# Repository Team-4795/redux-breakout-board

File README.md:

# rio-RGB_LED-buffer-board
a pcb that mounts to a RoboRIO and buffers the data stream for WS2812b and similar LED strips

The RoboRIO can generate a data stream for addressable "smart" LED
strips built from WS2812b and similar LEDs.  This data comes out on
one of the PWM ports, but is much faster than the typical "servo" PWM
data.  As such, it is more sensitive to signal integrity issues,
especially when splitting it to drive multiple LED strips with
identical data.

The tutorial and circuit board here is inspired by a discussion on the
Chief Delphi forums https://www.chiefdelphi.com/t/wrong-colors-from-ws2812-led-strips-driven-by-roborio/434199

The basic idea is that we use one WS2812b addressable LED as a
"buffer", to recieve the data stream from the RoboRIO, and retransmit
it downstream to one or more LED strips on the robot.

This has two benefits:
- The output from a WS2812b is more nearly optimized to drive further LEDs than the output of the Rio itself.
- We've always got a single LED on the RoboRIO for testing the RGB-output code, even when the other LED strips are disconnected.

References

https://docs.wpilib.org/en/stable/docs/software/hardware-apis/misc/addressable-leds.html

https://www.chiefdelphi.com/t/wrong-colors-from-ws2812-led-strips-driven-by-roborio/434199

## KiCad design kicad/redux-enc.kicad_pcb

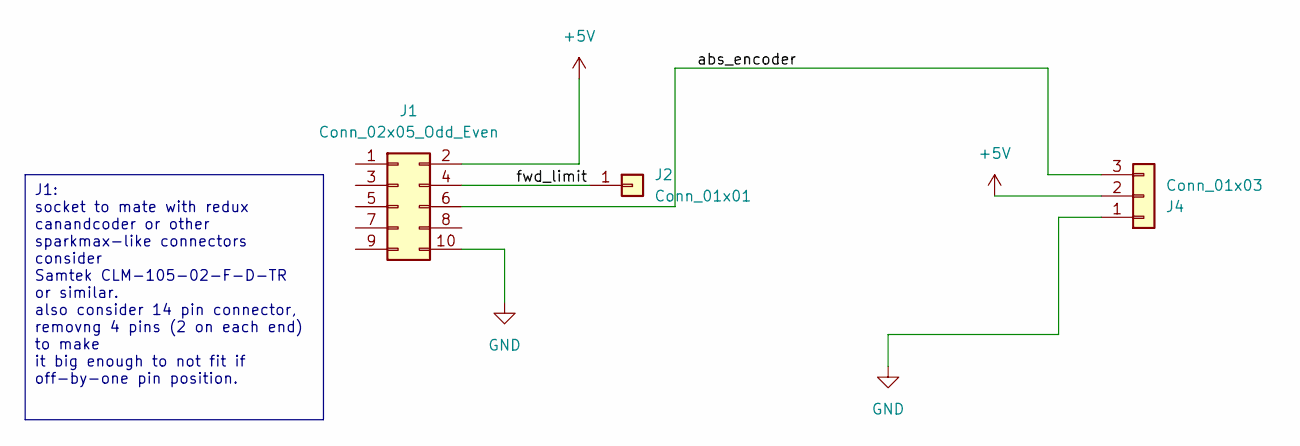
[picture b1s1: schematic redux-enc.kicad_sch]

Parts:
J1: Conn_02x05_Odd_Even; PinSocket_2x05_P1.00mm_Vertical_SMD
J2: Conn_01x01; PinHeader_1x01_P2.54mm_Vertical
J4: Conn_01x03; CONN_70555-0002_MOL

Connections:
+5V: J1.2, J4.2
/abs_encoder: J1.6, J4.3
/fwd_limit: J1.4, J2.1
GND: J1.10, J4.1

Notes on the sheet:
J1: socket to mate with redux canandcoder or other sparkmax-like connectors consider Samtek CLM-105-02-F-D-TR or similar. also consider 14 pin connector, removng 4 pins (2 on each end) to make it big enough to not fit if off-by-one pin position.

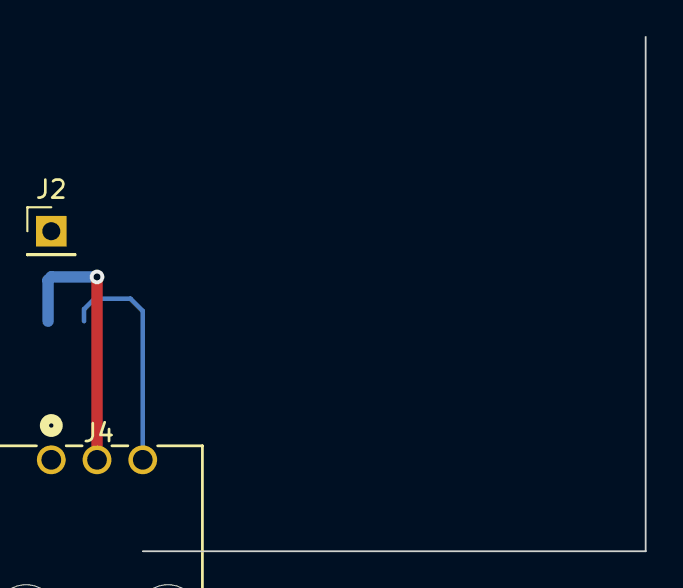
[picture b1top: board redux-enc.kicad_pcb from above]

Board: 2 copper layers, 3 parts (1 on the bottom side), 4 nets.

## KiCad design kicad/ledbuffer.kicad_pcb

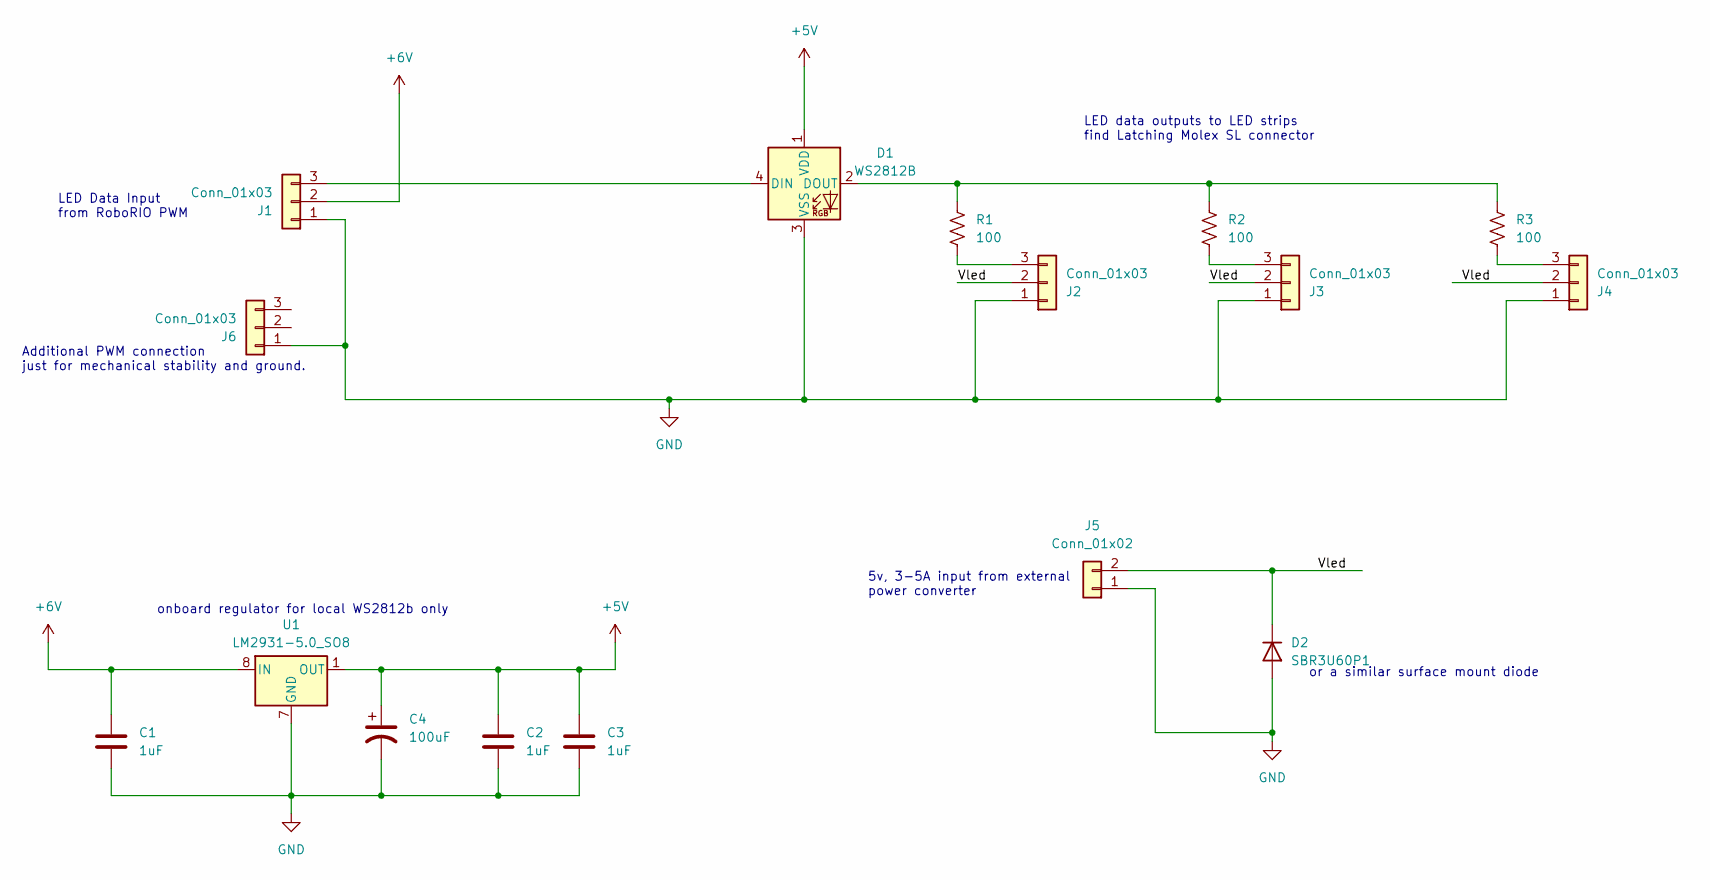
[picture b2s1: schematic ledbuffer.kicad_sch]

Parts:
C1, C2, C3: 1uF; C_0805_2012Metric_Pad1.18x1.45mm_HandSolder
C4: 100uF; C_1206_3216Metric_Pad1.33x1.80mm_HandSolder
D1: WS2812B; LED_WS2812B_PLCC4_5.0x5.0mm_P3.2mm
D2: SBR3U60P1; D_PowerDI-123
J1, J6: Conn_01x03; PinSocket_1x03_P2.54mm_Vertical
J2, J3, J4: Conn_01x03; CONN_70555-0002_MOL
J5: Conn_01x02; 26011102
R1, R2, R3: 100; R_0805_2012Metric_Pad1.20x1.40mm_HandSolder
U1: LM2931-5.0_SO8; SOIC-8_3.9x4.9mm_P1.27mm

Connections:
+5V: C2.1, C3.1, C4.1, D1.1 (VDD), U1.1 (OUT)
+6V: C1.1, J1.2, U1.8 (IN)
/Vled: D2.1 (K), J2.2, J3.2, J4.2, J5.2
GND: C1.2, C2.2, C3.2, C4.2, D1.3 (VSS), D2.2 (A), J1.1, J2.1, J3.1, J4.1, J5.1, J6.1, U1.2 (GND), U1.3 (GND), U1.6 (GND), U1.7 (GND)
unnamed: D1.4 (DIN), J1.3
unnamed: D1.2 (DOUT), R1.1, R2.1, R3.1
unnamed: J2.3, R1.2
unnamed: J3.3, R2.2
unnamed: J4.3, R3.2

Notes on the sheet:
or a similar surface mount diode
Additional PWM connection just for mechanical stability and ground.
onboard regulator for local WS2812b only
LED Data Input from RoboRIO PWM
LED data outputs to LED strips find Latching Molex SL connector
5v, 3-5A input from external power converter

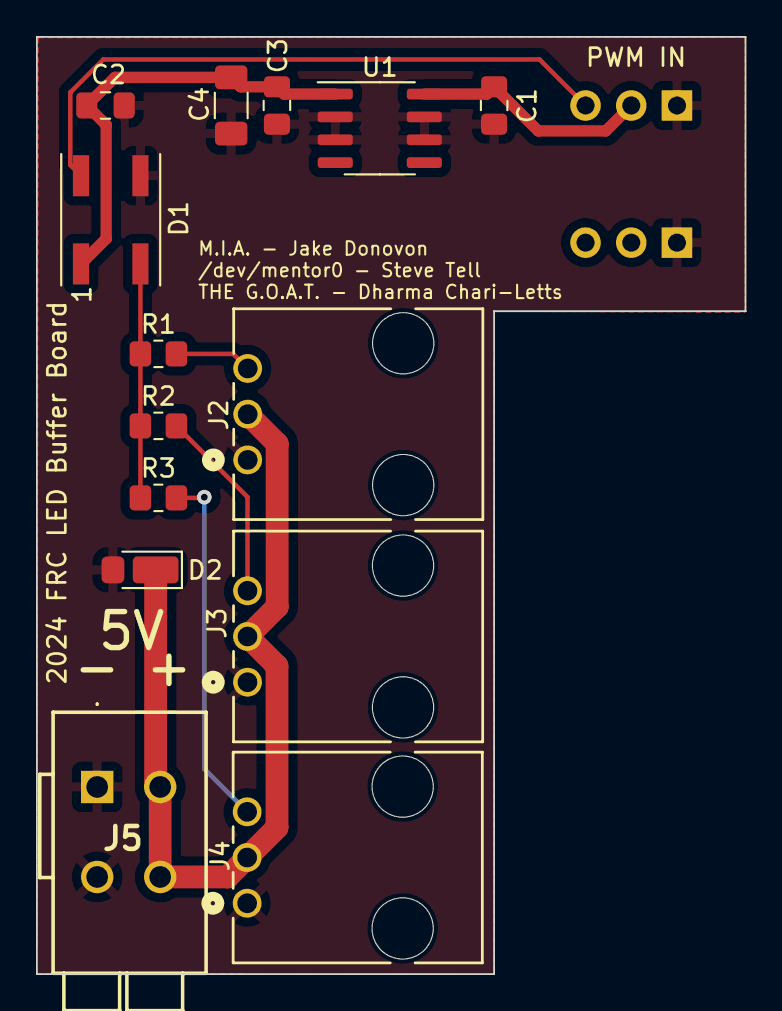
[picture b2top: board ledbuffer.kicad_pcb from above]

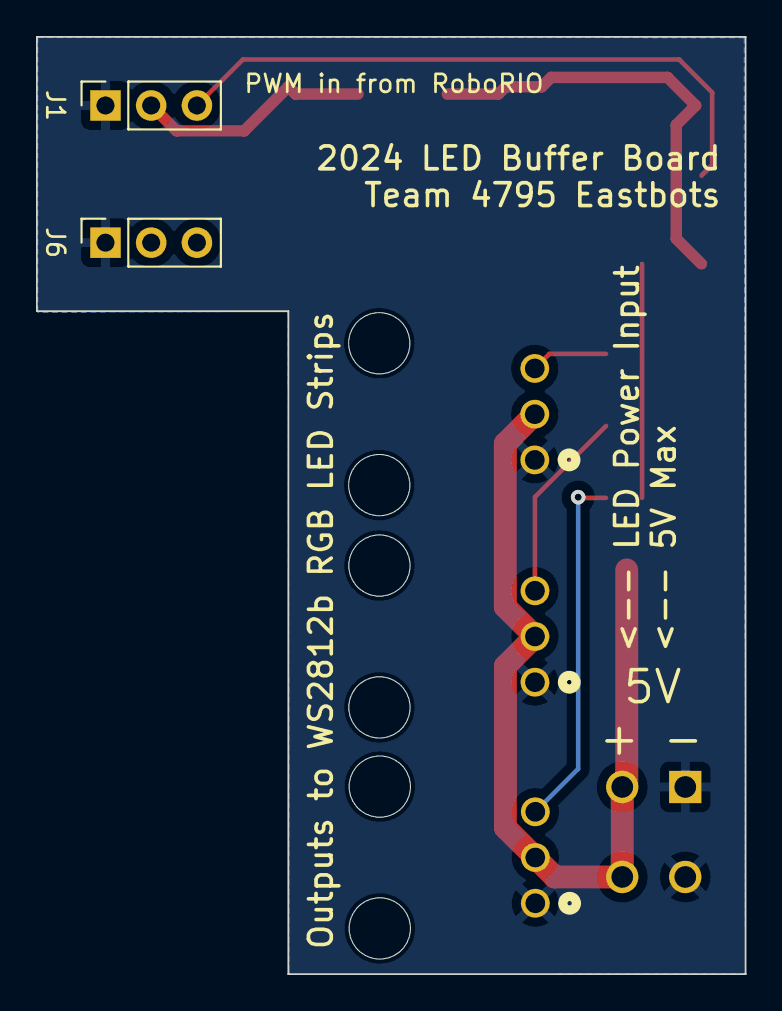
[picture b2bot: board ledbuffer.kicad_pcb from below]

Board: 2 copper layers, 39.4 x 52.1 mm, 16 parts (2 on the bottom side), 9 nets.

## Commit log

2024-02-02 Initial creation of led-buffer schematic import .git* control files initial schematic explain the rough idea in the README
2024-02-04 schematic updates, start doc/*, find footprints add a third output connector add power input connector, and polarity protection diode
2024-02-04 Added Wago 2601-1102 footprint
2024-02-05 candidate final schematic assigned footprints to all parts added more regulator output capacitors to satisfy datasheet requirements added another input connector. only ground used. only for mechanica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
2024-02-13 start pcb with just an outline and some markings in a user layer for where the input connectors would go
2024-02-13 started layout placement by Dharma
2024-02-14 placement tweaks, set up for routing moved a few things a little bit added net+via sizes and net classes a few sample routes
2024-02-17 added a wire.
2024-02-17 wires and text
2024-02-17 Board Final
    Adjusted Placement of R1-3 and Diode
    added silkscreen text
2024-02-26 documentation fixes only print out assembly drawing for top layer, add the pdf add pdf of schematic first crack at assembly instructions
2025-01-21 add redux-encoder files
2025-01-21 clean up ledbuffer remnants
